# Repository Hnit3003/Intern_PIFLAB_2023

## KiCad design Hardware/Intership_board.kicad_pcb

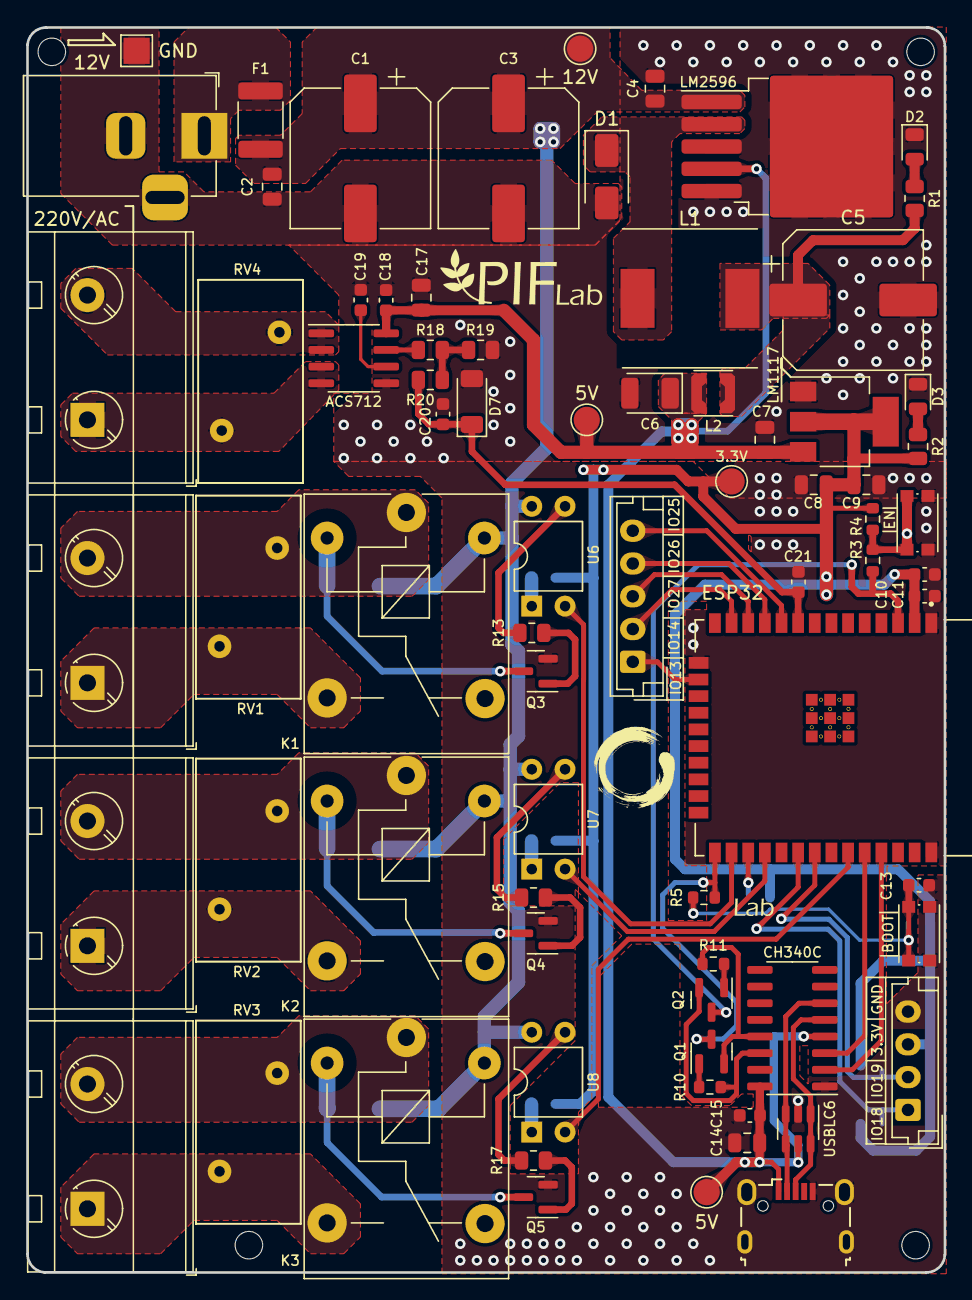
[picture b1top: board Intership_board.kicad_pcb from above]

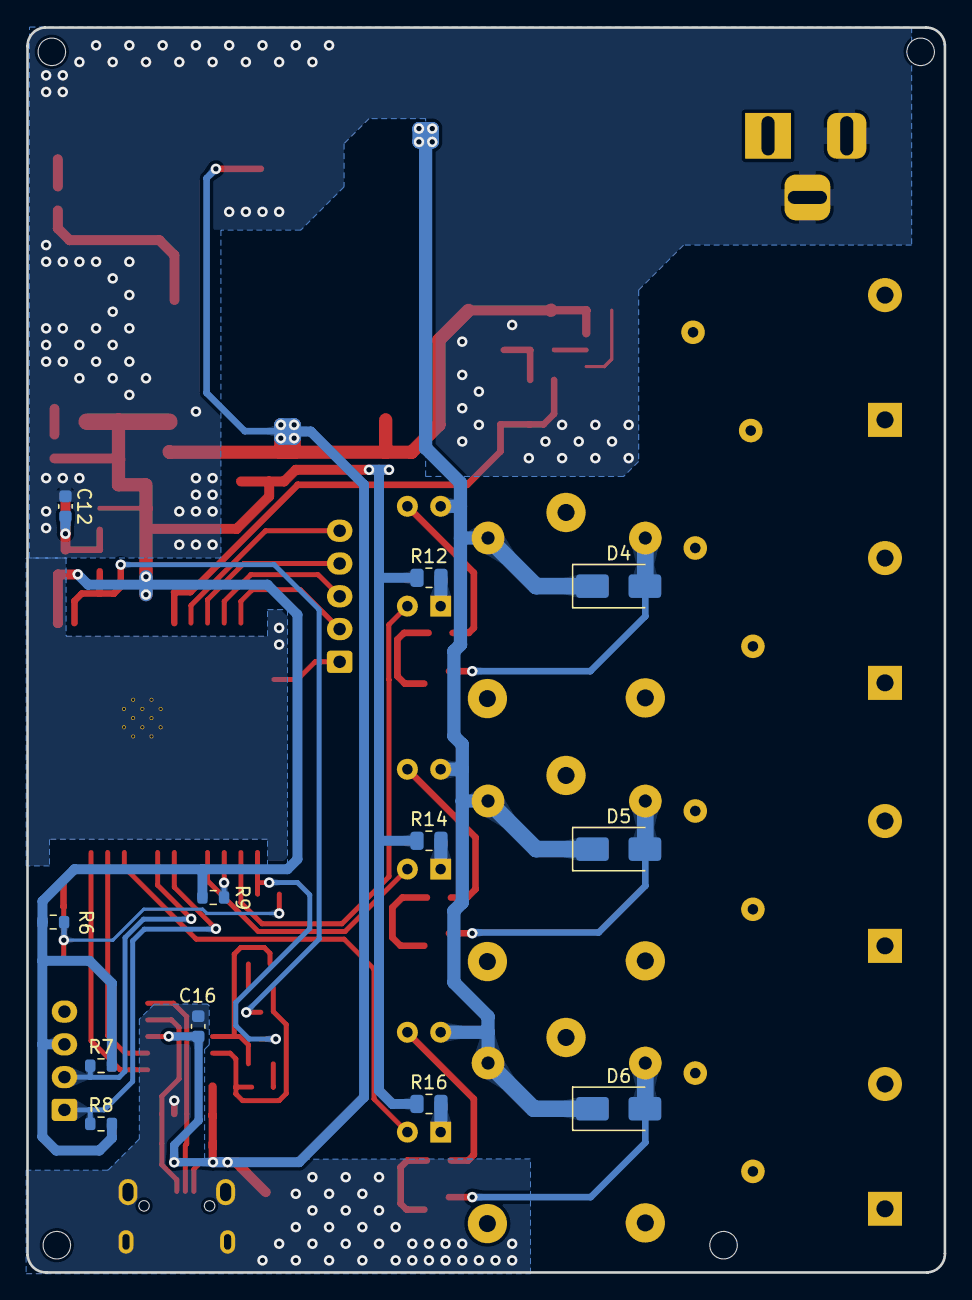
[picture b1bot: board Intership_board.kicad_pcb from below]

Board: 2 copper layers, 70.0 x 95.0 mm, 91 parts (12 on the bottom side), 56 nets.

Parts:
3.3V: 3.3VDC; TestPoint_Pad_D2.0mm
5V: USB_B_Mini; USB_Micro-B_Wuerth_629105150521
5V#2: VBUS; TestPoint_Pad_D2.0mm
5V#3: 5VDC; TestPoint_Pad_D2.0mm
12V: 12VDC/2~3mA; BarrelJack_Horizontal
12V#2: 12VDC; TestPoint_Pad_D2.0mm
220V/AC: Load 220V/AC; TerminalBlock_MetzConnect_Type703_RT10N02HGLU_1x02_P9.52mm_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
ACS712: ACS712xLCTR-20A; SOIC-8_3.9x4.9mm_P1.27mm
BOOT: SW_Push; SW_Push_1P1T_NO_CK_KMR2
C1, C3: 470uF/35V; CP_Elec_10x10.5
C2, C4: 0.1uF/50V; C_0805_2012Metric
C5: 330uF/35V; CP_Elec_10x10.5
C6: 220uF/16V; CP_EIA-3528-12_Kemet-T
C7, C14: 10uF/25V; C_0805_2012Metric
C8, C17: 22uF/16V; C_0805_2012Metric
C9: 100nF/50V; C_0805_2012Metric
C10: 10uF/25V; C_0603_1608Metric
C11, C12, C13, C15, C16, C18, C19, C21: 100nF/50V; C_0603_1608Metric
C20: 500nF/25V; C_0603_1608Metric
CH340C: CH340C; SOIC-16_3.9x9.9mm_P1.27mm
D1: SS34/3A; D_SMA
D2, D3: LED; LED_0805_2012Metric
D4, D5, D6: SS210/2A/100V; D_SMA
D7: ZMM3V3; D_MiniMELF
EN: SW_Push; SW_Push_1P1T_NO_CK_KMR2
ESP32: ESP32-WROOM-32E; XCVR_ESP32-WROOM-32E
F1: 500mA; Fuse_1812_4532Metric_Pad1.30x3.40mm_HandSolder
GND: Earth; TestPoint_Pad_2.0x2.0mm
H1, H3, H4: Through Hole; MountingHole_2.1mm
H2: Through hole; MountingHole_2.1mm
J2: Conn_01x04_Pin; JST_EH_B4B-EH-A_1x04_P2.50mm_Vertical
J3: Conn_01x05_Pin; JST_EH_B5B-EH-A_1x05_P2.50mm_Vertical
J5, J6, J7: Load 220V/AC; TerminalBlock_MetzConnect_Type703_RT10N02HGLU_1x02_P9.52mm_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
K1, K2, K3: SRD-12VDC-SL-C; Relay_SPDT_SANYOU_SRD_Series_Form_C
L1: 68uH/2.08A; L_Taiyo-Yuden_NR-10050_9.8x10.0mm
L2: 3uH/2.2A; L_Coilcraft_LPS3010
LM1117: LM1117MP-3.3; SOT-223-3_TabPin2
LM2596: LM2596S-ADJ; TO-263-5_TabPin3
Q1, Q2: BC817; SOT-23
Q3, Q4, Q5: MMBTA42/300V/0.5mA; SOT-23
R1, R2, R18, R19: 1k; R_0805_2012Metric
R3, R5: 0; R_0603_1608Metric
R4, R6, R7, R8, R9, R10, R11: 10k; R_0603_1608Metric
R12, R14, R16: 200; R_0805_2012Metric
R13, R15, R17: 2.2k; R_0805_2012Metric
R20: 2.1k; R_0805_2012Metric
RV1, RV2, RV3, RV4: 420L40/680V; RV_Disc_D15.5mm_W8mm_P7.5mm
U6, U7, U8: PC817; DIP-4_W7.62mm
USBLC6: USBLC6-2SC6; SOT-23-6

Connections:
3.3VDC: 3.3V.1, C8.1, C9.1, C10.1, C11.1, ESP32.2 (VDD), J2.3, LM1117.2 (VO), R2.1, R4.2, R6.2, R7.2, R8.2, R9.2, R12.1, R14.1, R16.1
5VDC: 5V.1 (VBUS), 5V#2.1, 5V#3.1, ACS712.8 (VCC), C6.1, C7.1, C14.2, C15.2, C16.1, C17.2, C18.2, CH340C.4 (V3), CH340C.16 (VCC), L2.2, LM1117.3 (VI), LM2596.4 (FB), USBLC6.5 (VBUS)
12VDC: 12V#2.1, C1.1, C2.1, C3.1, C4.1, D4.1 (K), D5.1 (K), D6.1 (K), F1.2, K1.5, K2.5, K3.5, LM2596.1 (VIN), U6.4, U7.4, U8.4
DTR: CH340C.13 (~DTR), Q1.2 (E), R11.1
ESP_EN: ESP32.3 (EN), Q2.3 (C), R3.2
ESP_IO0: ESP32.25 (IO0), Q1.3 (C), R5.1
ESP_IO18: ESP32.30 (IO18), J2.1, R8.1
ESP_IO19: ESP32.31 (IO19), J2.2, R7.1
ESP_IO25: ESP32.10 (IO25), J3.5
ESP_IO26: ESP32.11 (IO26), J3.4
ESP_IO27: ESP32.12 (IO27), J3.3
ESP_IO_ADC2_CH0: C20.2, C21.2, D7.1 (K), ESP32.9 (IO33), R20.2
ESP_IO_Relay_1: ESP32.26 (IO4), U6.2
ESP_IO_Relay_2: ESP32.28 (IO17), U7.2
ESP_IO_Relay_3: ESP32.33 (IO21), U8.2
ESP_MOSI: ESP32.16 (IO13), J3.1
ESP_RXD: CH340C.3 (RXD), ESP32.34 (RXD0/IO3)
ESP_SCLK: ESP32.13 (IO14), J3.2
ESP_TXD: CH340C.2 (TXD), ESP32.35 (TXD0/IO1)
Earth: 5V.5 (GND), 5V.6 (Shield), 12V.2, 12V.3, ACS712.5 (GND), BOOT.2, C1.2, C2.2, C3.2, C4.2, C5.2, C6.2, C7.2, C8.2, C9.2, C10.2, C11.2, C12.1, C13.2, C14.1, C15.1, C16.2, C17.1, C18.1, C19.1, C20.1, C21.1, CH340C.1 (GND), D1.2 (A), D2.1 (K), D3.1 (K), D7.2 (A), EN.1, ESP32.1 (GND), ESP32.15 (GND), ESP32.38 (GND), ESP32.39_10, ESP32.39_11, ESP32.39_12, ESP32.39_13, ESP32.39_14, ESP32.39_15, ESP32.39_16, ESP32.39_17, ESP32.39_18, ESP32.39_19, ESP32.39_20, ESP32.39_21, GND.1, J2.4, LM1117.1 (GND), LM2596.3 (GND), LM2596.5 (~ON/OFF), Q3.2 (E), Q4.2 (E), Q5.2 (E), R19.1, USBLC6.2 (GND)
unnamed: C5.1, L1.2, L2.1, R1.1
unnamed: C12.2, EN.2, R3.1, R4.1
unnamed: BOOT.1, C13.1, R5.2, R6.1
unnamed: D1.1 (K), L1.1, LM2596.2 (OUT)
unnamed: D2.2 (A), R1.2
unnamed: D3.2 (A), R2.2
unnamed: D4.2 (A), K1.2, Q3.3 (C)
unnamed: D5.2 (A), K2.2, Q4.3 (C)
unnamed: D6.2 (A), K3.2, Q5.3 (C)
unnamed: 12V.1, F1.1
unnamed: 5V.3 (D+), CH340C.5 (UD+), USBLC6.1 (I/O1), USBLC6.6 (I/O1)
unnamed: 5V.2 (D-), CH340C.6 (UD-), USBLC6.3 (I/O2), USBLC6.4 (I/O2)
unnamed: J5.1, K1.3, RV1.1
unnamed: J5.2, K1.1, RV1.2
unnamed: J6.1, K2.3, RV2.1
unnamed: J6.2, K2.1, RV2.2
unnamed: J7.1, K3.3, RV3.1
unnamed: J7.2, K3.1, RV3.2
unnamed: 220V/AC.1, ACS712.3 (IP-), ACS712.4 (IP-), RV4.2
unnamed: 220V/AC.2, ACS712.1 (IP+), ACS712.2 (IP+), RV4.1
unnamed: Q1.1 (B), R10.2
unnamed: Q2.1 (B), R11.2
unnamed: Q3.1 (B), R13.2
unnamed: Q4.1 (B), R15.2
unnamed: Q5.1 (B), R17.2
unnamed: R12.2, U6.1
unnamed: R13.1, U6.3
unnamed: R14.2, U7.1
unnamed: R15.1, U7.3
unnamed: R16.2, U8.1
unnamed: R17.1, U8.3
unnamed: R18.2, R19.2, R20.1
unnamed: ESP32.27 (IO16), R9.1
unnamed: ACS712.6 (FILTER), C19.2
unnamed: ACS712.7 (VIOUT), R18.1
RTS: CH340C.14 (~RTS), Q2.2 (E), R10.1

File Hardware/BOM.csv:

"Id";"Designator";"Footprint";"Quantity";"Designation";"Supplier and ref";
1;"R5,R3";"R_0603_1608Metric";2;"0";;;
2;"H4,H3,H1";"MountingHole_2.1mm";3;"Through Hole";;;
3;"EN,BOOT";"SW_Push_1P1T_NO_CK_KMR2";2;"SW_Push";;;
4;"K3,K2,K1";"Relay_SPDT_SANYOU_SRD_Series_Form_C";3;"SRD-12VDC-SL-C";;;
5;"RV2,RV3,RV4,RV1";"RV_Disc_D15.5mm_W8mm_P7.5mm";4;"420L40/680V";;;
6;"ACS712";"SOIC-8_3.9x4.9mm_P1.27mm";1;"ACS712xLCTR-20A";;;
7;"C2,C4";"C_0805_2012Metric";2;"0.1uF/50V";;;
8;"U6,U8,U7";"DIP-4_W7.62mm";3;"PC817";;;
9;"J2";"JST_EH_B4B-EH-A_1x04_P2.50mm_Vertical";1;"Conn_01x04_Pin";;;
10;"J7,J5,220V/AC,J6";"TerminalBlock_MetzConnect_Type703_RT10N02HGLU_1x02_P9.52mm_Horizontal";4;"Load 220V/AC";;;
11;"C10";"C_0603_1608Metric";1;"10uF/25V";;;
12;"J3";"JST_EH_B5B-EH-A_1x05_P2.50mm_Vertical";1;"Conn_01x05_Pin";;;
13;"C17,C8";"C_0805_2012Metric";2;"22uF/16V";;;
14;"12V";"BarrelJack_Horizontal";1;"12VDC/2~3mA";;;
15;"R15,R13,R17";"R_0805_2012Metric";3;"2.2k";;;
16;"C20";"C_0603_1608Metric";1;"500nF/25V";;;
17;"R19,R1,R18,R2";"R_0805_2012Metric";4;"1k";;;
18;"ESP32";"XCVR_ESP32-WROOM-32E";1;"ESP32-WROOM-32E";;;
19;"C11,C15,C19,C18,C13,C21,C12,C16";"C_0603_1608Metric";8;"100nF/50V";;;
20;"Q5,Q4,Q3";"SOT-23";3;"MMBTA42/300V/0.5mA";;;
21;"D7";"D_MiniMELF";1;"ZMM3V3";;;
22;"C6";"CP_EIA-3528-12_Kemet-T";1;"220uF/16V";;;
23;"LM2596";"TO-263-5_TabPin3";1;"LM2596S-ADJ";;;
24;"L2";"L_Coilcraft_LPS3010";1;"3uH/2.2A";;;
25;"H2";"MountingHole_2.1mm";1;"Through hole";;;
26;"F1";"Fuse_1812_4532Metric_Pad1.30x3.40mm_HandSolder";1;"500mA";;;
27;"C9";"C_0805_2012Metric";1;"100nF/50V";;;
28;"D3,D2";"LED_0805_2012Metric";2;"LED";;;
29;"12V";"TestPoint_Pad_D2.0mm";1;"12VDC";;;
30;"R10,R11,R4,R6,R8,R9,R7";"R_0603_1608Metric";7;"10k";;;
31;"3.3V";"TestPoint_Pad_D2.0mm";1;"3.3VDC";;;
32;"5V";"USB_Micro-B_Wuerth_629105150521";1;"USB_B_Mini";;;
33;"Q1,Q2";"SOT-23";2;"BC817";;;
34;"LM1117";"SOT-223-3_TabPin2";1;"LM1117MP-3.3";;;
35;"D1";"D_SMA";1;"SS34/3A";;;
36;"USBLC6";"SOT-23-6";1;"USBLC6-2SC6";;;
37;"L1";"L_Taiyo-Yuden_NR-10050_9.8x10.0mm";1;"68uH/2.08A";;;
38;"R20";"R_0805_2012Metric";1;"2.1k";;;
39;"C7,C14";"C_0805_2012Metric";2;"10uF/25V";;;
40;"CH340C";"SOIC-16_3.9x9.9mm_P1.27mm";1;"CH340C";;;
41;"GND";"TestPoint_Pad_2.0x2.0mm";1;"Earth";;;
42;"C3,C1";"CP_Elec_10x10.5";2;"470uF/35V";;;
43;"5V";"TestPoint_Pad_D2.0mm";1;"VBUS";;;
44;"C5";"CP_Elec_10x10.5";1;"330uF/35V";;;
45;"5V";"TestPoint_Pad_D2.0mm";1;"5VDC";;;
46;"D5,D6,D4";"D_SMA";3;"SS210/2A/100V";;;
47;"R12,R14,R16";"R_0805_2012Metric";3;"200";;;

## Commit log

2023-08-09 [Tinh Chau] complete Intern project in PIFLAB
